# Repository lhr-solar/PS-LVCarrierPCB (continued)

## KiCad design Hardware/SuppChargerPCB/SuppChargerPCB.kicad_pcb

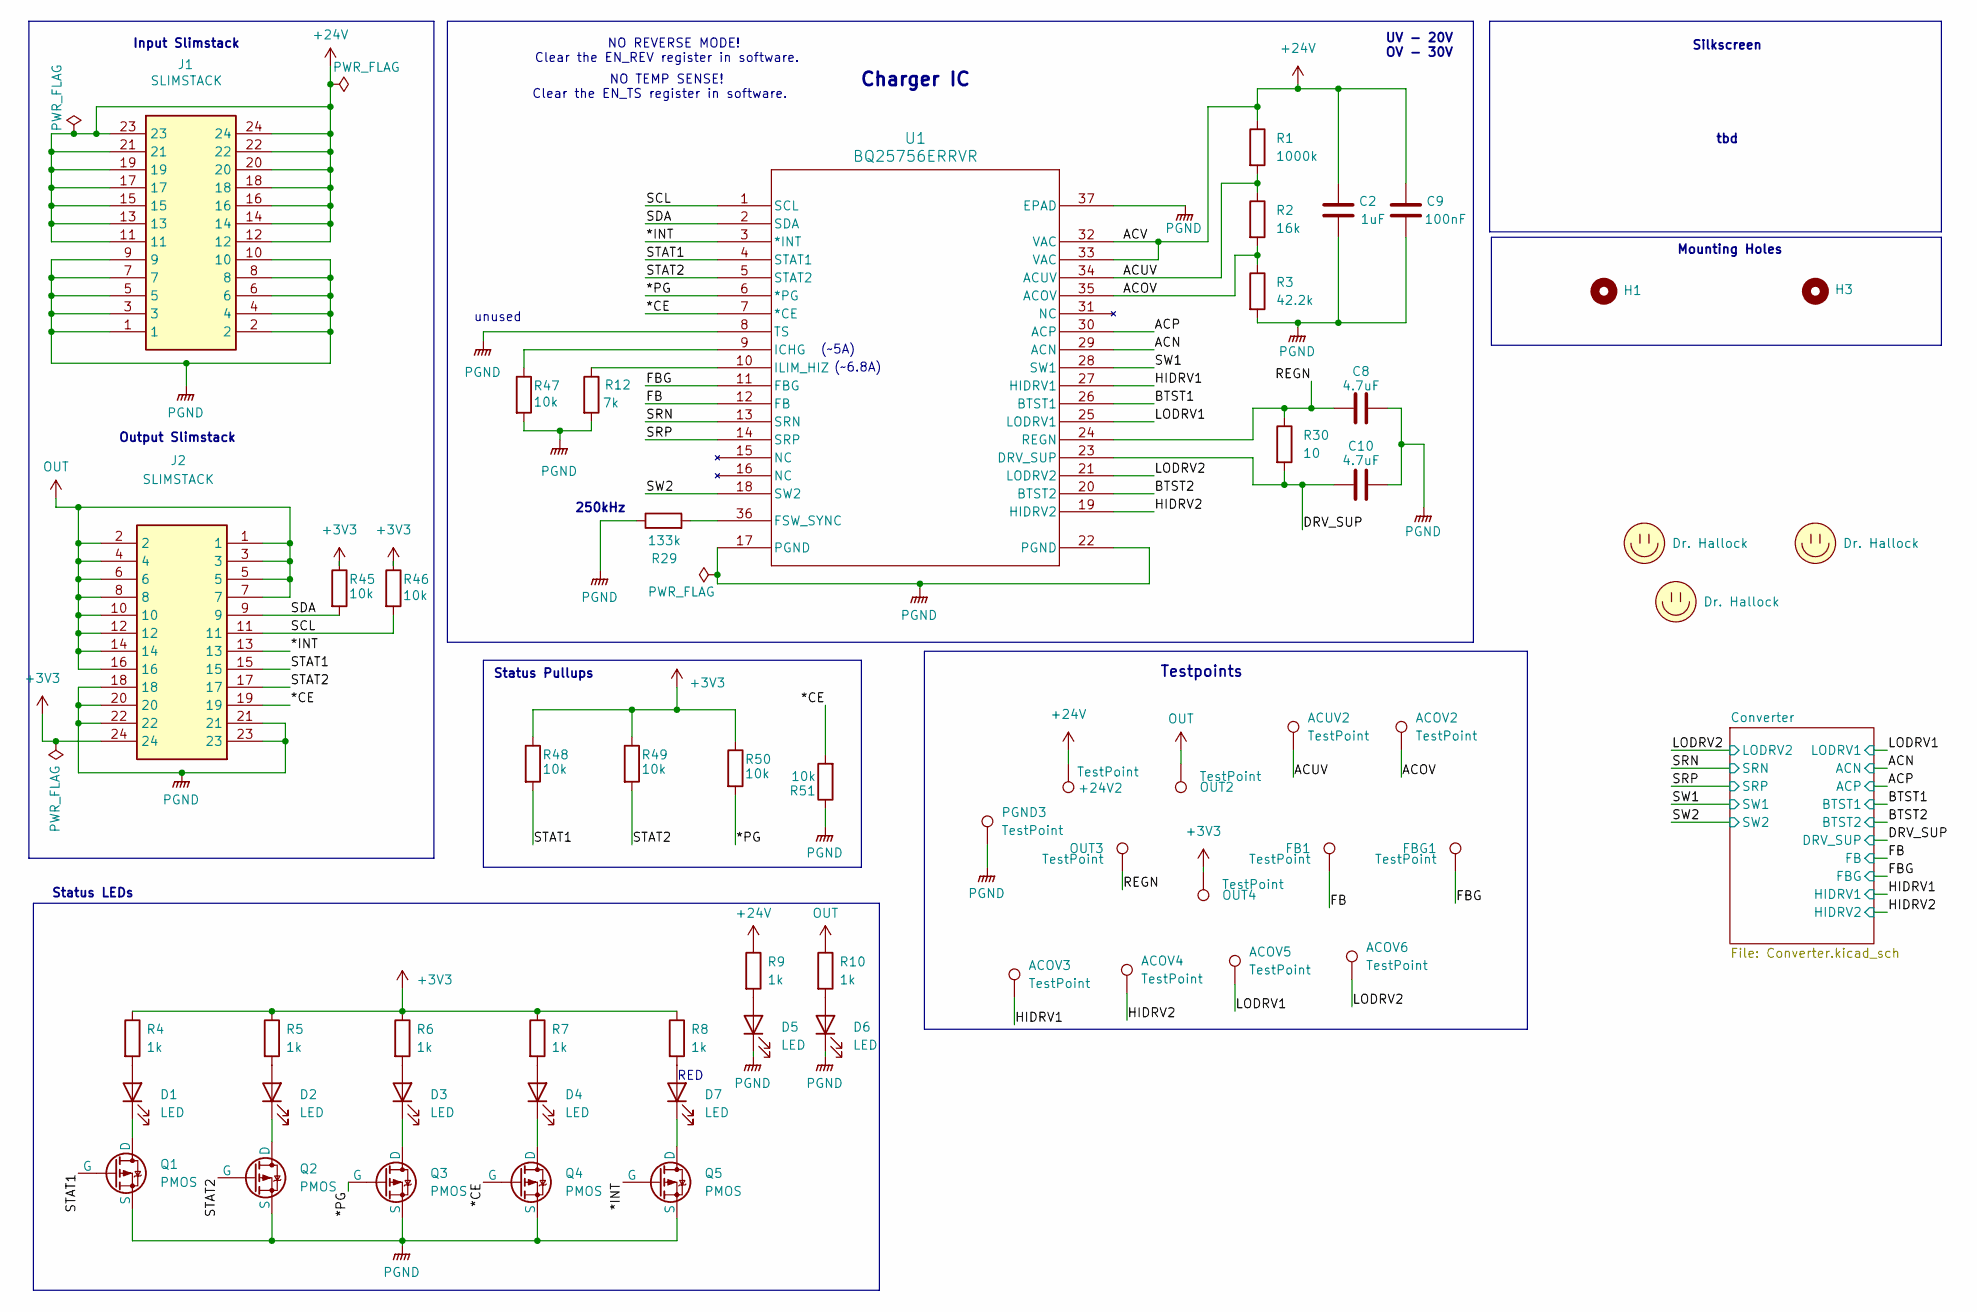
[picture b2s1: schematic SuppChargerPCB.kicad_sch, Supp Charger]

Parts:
+24V2: TestPoint; TestPoint_THTPad_1.0x1.0mm_Drill0.5mm
ACOV2, ACOV3, ACOV4, ACOV5, ACOV6: TestPoint; TestPoint_Pad_1.0x1.0mm
ACUV2: TestPoint; TestPoint_Pad_1.0x1.0mm
C2: 1uF; C_0603_1608Metric_Pad1.08x0.95mm_HandSolder
C8, C10: 4.7uF; C_0805_2012Metric
C9: 100nF; C_0603_1608Metric_Pad1.08x0.95mm_HandSolder
D1, D2, D3, D4, D5, D6, D7: LED; D_0603_1608Metric
FB1: TestPoint; TestPoint_Pad_1.0x1.0mm
FBG1: TestPoint; TestPoint_Pad_1.0x1.0mm
H1, H3: MountingHole; MountingHole_3.2mm_M3_Pad_TopBottom
J1, J2: SLIMSTACK; 524652470; Mouser Part Number 538-52465-2470
LOGO1: Dr. Hallock; UTSVT_Logo_Symbol
LOGO2: Dr. Hallock; LHRs_LOGO
LOGO3: Dr. Hallock; Hallock_Image_Tiny
OUT2, OUT4: TestPoint; TestPoint_THTPad_1.0x1.0mm_Drill0.5mm
OUT3: TestPoint; TestPoint_Pad_1.0x1.0mm
PGND3: TestPoint; TestPoint_THTPad_1.0x1.0mm_Drill0.5mm
Q1, Q2, Q3, Q4, Q5: PMOS; SOT-23
R1: 1000k; R_0603_1608Metric_Pad0.98x0.95mm_HandSolder
R2: 16k; R_0603_1608Metric_Pad0.98x0.95mm_HandSolder
R3: 42.2k; R_0603_1608Metric_Pad0.98x0.95mm_HandSolder
R4, R5, R6, R7, R8, R9, R10: 1k; R_0603_1608Metric_Pad0.98x0.95mm_HandSolder
R12: 7k; R_0603_1608Metric_Pad0.98x0.95mm_HandSolder
R29: 133k; R_0603_1608Metric_Pad0.98x0.95mm_HandSolder
R30: 10; R_0603_1608Metric_Pad0.98x0.95mm_HandSolder
R45, R46, R47, R48, R49, R50, R51: 10k; R_0603_1608Metric_Pad0.98x0.95mm_HandSolder
U1: BQ25756ERRVR; VQFN36_RRV_TEX

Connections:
+3V3: J2.24, OUT4.1, R4.1, R5.1, R6.1, R7.1, R8.1, R45.1, R46.1, R48.1, R49.1, R50.1
+24V: +24V2.1, C2.1, C9.1, J1.11, J1.12, J1.13, J1.14, J1.15, J1.16, J1.17, J1.18, J1.19, J1.20, J1.21, J1.22, J1.23, J1.24, R1.1, R9.1, U1.32 (VAC), U1.33 (VAC); also elsewhere on the board
/*CE: J2.19, Q4.2 (G), R51.2, U1.7 (*CE)
/*INT: J2.13, Q5.2 (G), U1.3 (*INT)
/*PG: Q3.2 (G), R50.2, U1.6 (*PG)
/ACN: U1.29 (ACN); also elsewhere on the board
/ACOV: ACOV2.1, R2.2, R3.1, U1.35 (ACOV)
/ACP: U1.30 (ACP); also elsewhere on the board
/ACUV: ACUV2.1, R1.2, R2.1, U1.34 (ACUV)
/BTST1: U1.26 (BTST1); also elsewhere on the board
/BTST2: U1.20 (BTST2); also elsewhere on the board
/DRV_SUP: C10.1, R30.2, U1.23 (DRV_SUP); also elsewhere on the board
/FB: FB1.1, U1.12 (FB); also elsewhere on the board
/FBG: FBG1.1, U1.11 (FBG); also elsewhere on the board
/HIDRV1: ACOV3.1, U1.27 (HIDRV1); also elsewhere on the board
/HIDRV2: ACOV4.1, U1.19 (HIDRV2); also elsewhere on the board
/LODRV1: ACOV5.1, U1.25 (LODRV1); also elsewhere on the board
/LODRV2: ACOV6.1, U1.21 (LODRV2); also elsewhere on the board
/REGN: C8.1, OUT3.1, R30.1, U1.24 (REGN)
/SCL: J2.11, R46.2, U1.1 (SCL)
/SDA: J2.9, R45.2, U1.2 (SDA)
/SRN: U1.13 (SRN); also elsewhere on the board
/SRP: U1.14 (SRP); also elsewhere on the board
/STAT1: J2.15, Q1.2 (G), R48.2, U1.4 (STAT1)
/STAT2: J2.17, Q2.2 (G), R49.2, U1.5 (STAT2)
/SW1: U1.28 (SW1); also elsewhere on the board
/SW2: U1.18 (SW2); also elsewhere on the board
unnamed: D1.2 (A), R4.2
unnamed: D1.1 (K), Q1.1 (D)
unnamed: D2.2 (A), R5.2
unnamed: D2.1 (K), Q2.1 (D)
unnamed: D3.2 (A), R6.2
unnamed: D3.1 (K), Q3.1 (D)
unnamed: D4.2 (A), R7.2
unnamed: D4.1 (K), Q4.1 (D)
unnamed: D5.2 (A), R9.2
unnamed: D6.2 (A), R10.2
unnamed: D7.2 (A), R8.2
unnamed: D7.1 (K), Q5.1 (D)
unnamed: R29.2, U1.36 (FSW_SYNC)
unnamed: R47.1, U1.9 (ICHG)
unnamed: R12.1, U1.10 (ILIM_HIZ)
OUT: J2.1, J2.2, J2.3, J2.4, J2.5, J2.6, J2.7, J2.8, J2.10, J2.12, J2.14, J2.16, OUT2.1, R10.1; also elsewhere on the board
PGND: C2.2, C8.2, C9.2, C10.2, D5.1 (K), D6.1 (K), J1.1, J1.2, J1.3, J1.4, J1.5, J1.6, J1.7, J1.8, J1.9, J1.10, J2.18, J2.20, J2.21, J2.22, J2.23, PGND3.1, Q1.3 (S), Q2.3 (S), Q3.3 (S), Q4.3 (S), Q5.3 (S), R3.2, R12.2, R29.1, R47.2, R51.1, U1.8 (TS), U1.17 (PGND), U1.22 (PGND), U1.37 (EPAD); also elsewhere on the board

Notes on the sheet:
Testpoints
(~6.8A)
250kHz
Mounting Holes
RED
Status LEDs
Status Pullups
Charger IC
unused
tbd
UV - 20V OV - 30V
Output Slimstack
NO REVERSE MODE! Clear the EN_REV register in software.
Input Slimstack
(~5A)
Silkscreen
NO TEMP SENSE! Clear the EN_TS register in software.

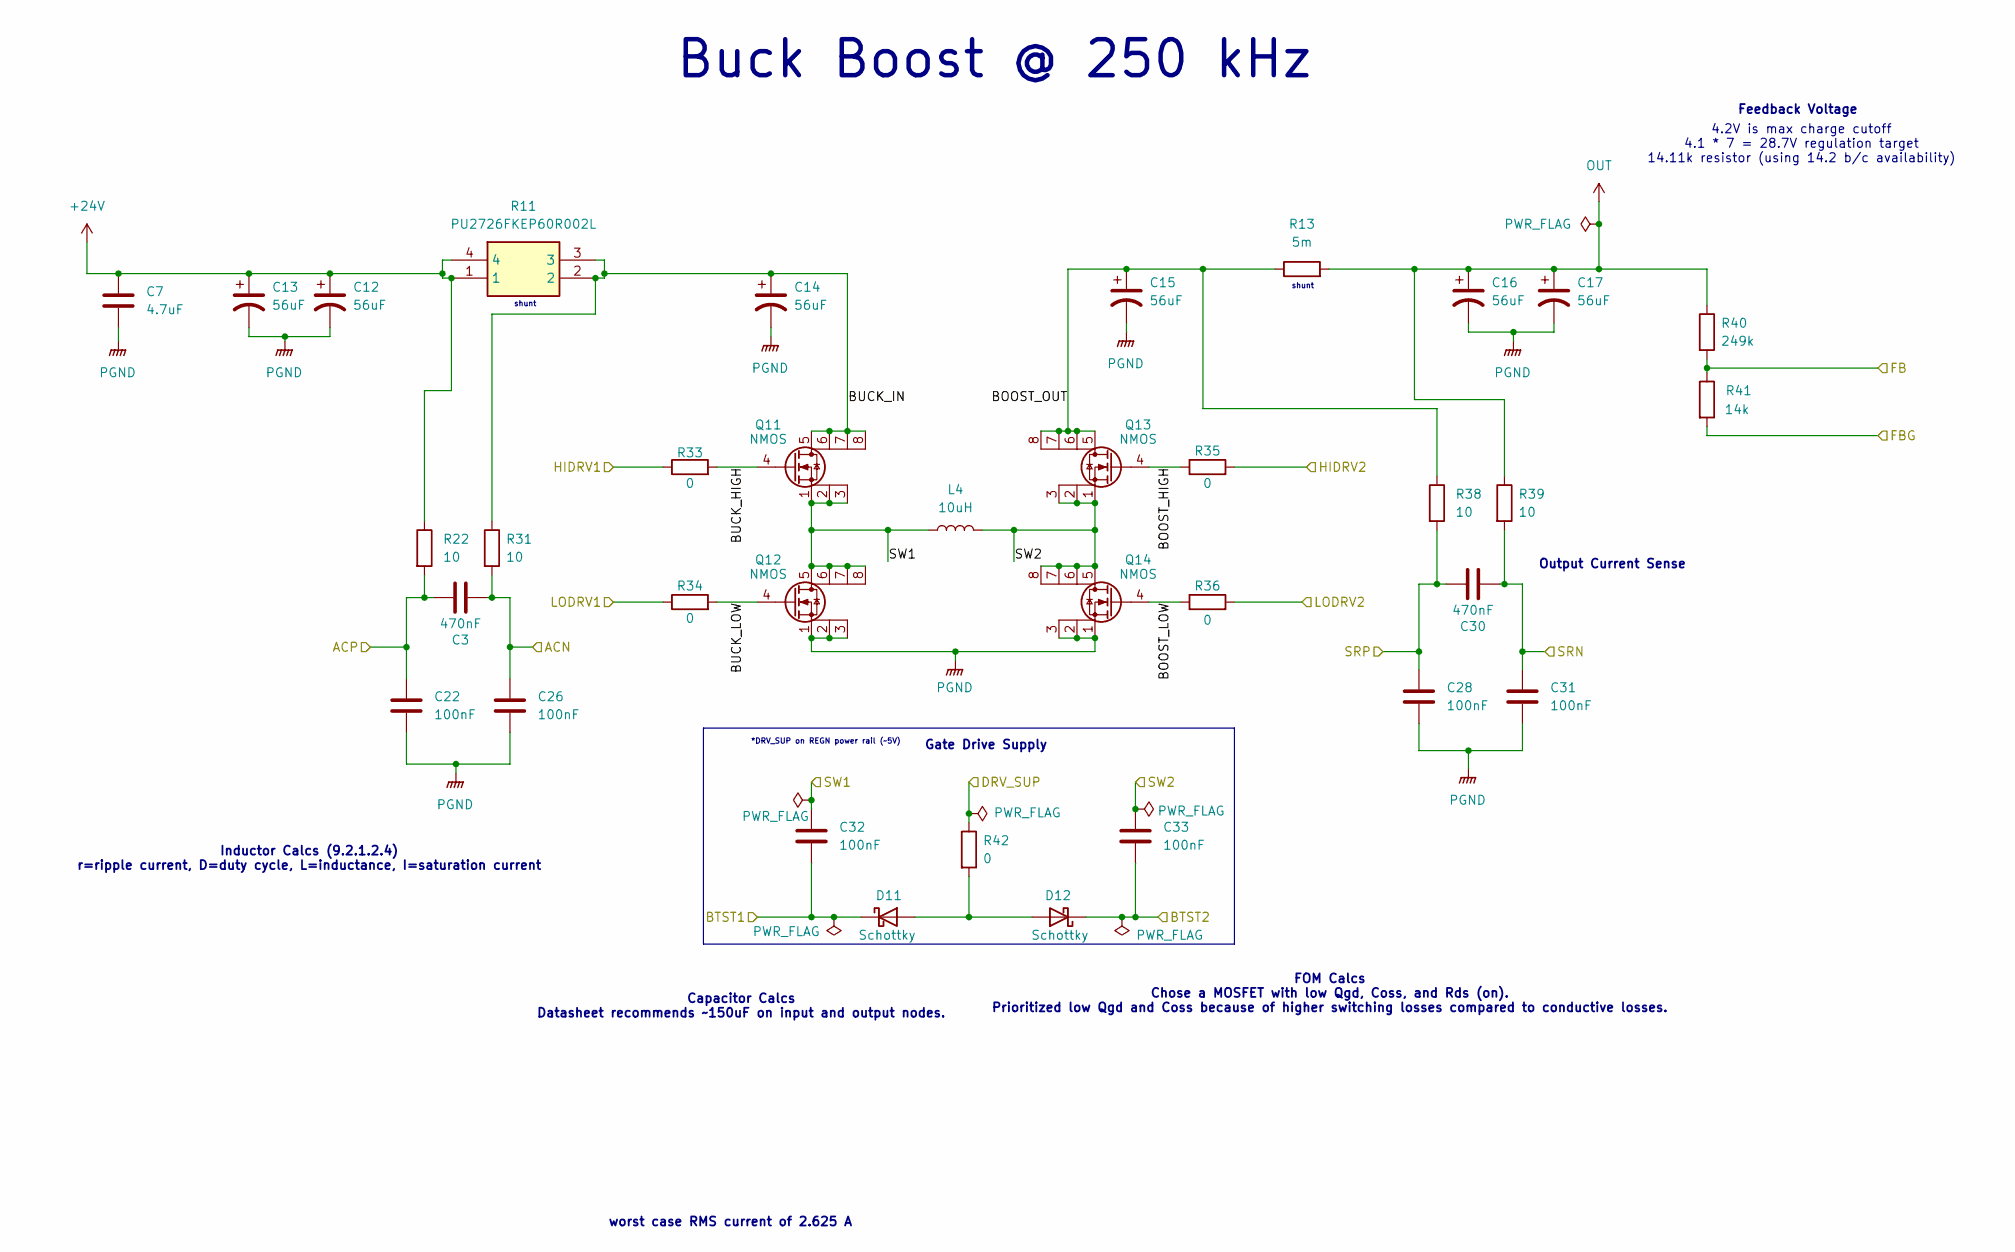
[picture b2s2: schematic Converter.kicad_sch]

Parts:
C3, C30: 470nF; C_0603_1608Metric_Pad1.08x0.95mm_HandSolder
C7: 4.7uF; C_0805_2012Metric
C12, C13, C14, C15, C16, C17: 56uF; CAPAE660X550N
C22, C26, C28, C31, C32, C33: 100nF; C_0603_1608Metric_Pad1.08x0.95mm_HandSolder
D11, D12: Schottky; D_SOD-123F
L4: 10uH; WE-HCC_807021
Q11, Q12, Q13, Q14: NMOS; MOSFET_3DN-T1-GE3_VIS
R11: PU2726FKEP60R002L; Manufacturer_Part_Number PU2726FKEP60R002L
R13: 5m; R_1210_3225Metric_Pad1.30x2.65mm_HandSolder
R22, R31, R38, R39: 10; R_0603_1608Metric_Pad0.98x0.95mm_HandSolder
R33, R34, R35, R36, R42: 0; R_0603_1608Metric_Pad0.98x0.95mm_HandSolder
R40: 249k; R_0603_1608Metric_Pad0.98x0.95mm_HandSolder
R41: 14k; R_0603_1608Metric_Pad0.98x0.95mm_HandSolder

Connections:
+24V: C7.1, C12.1, C13.1, R11.1, R11.4, R22.1; also elsewhere on the board
/ACN: C3.1, C26.1, R31.2; also elsewhere on the board
/ACP: C3.2, C22.1, R22.2; also elsewhere on the board
/BTST1: C32.2, D11.1 (K); also elsewhere on the board
/BTST2: C33.2, D12.1 (K); also elsewhere on the board
/Converter/BOOST_HIGH: Q13.4 (G), R35.1
/Converter/BOOST_LOW: Q14.4 (G), R36.1
/Converter/BOOST_OUT: C15.1, Q13.5 (D), Q13.6 (D), Q13.7 (D), Q13.8 (D), R13.1, R38.1
/Converter/BUCK_HIGH: Q11.4 (G), R33.2
/Converter/BUCK_IN: C14.1, Q11.5 (D), Q11.6 (D), Q11.7 (D), Q11.8 (D), R11.2, R11.3, R31.1
/Converter/BUCK_LOW: Q12.4 (G), R34.2
/DRV_SUP: R42.1; also elsewhere on the board
/FB: R40.2, R41.1; also elsewhere on the board
/FBG: R41.2; also elsewhere on the board
/HIDRV1: R33.1; also elsewhere on the board
/HIDRV2: R35.2; also elsewhere on the board
/LODRV1: R34.1; also elsewhere on the board
/LODRV2: R36.2; also elsewhere on the board
/SRN: C30.1, C31.1, R39.2; also elsewhere on the board
/SRP: C28.1, C30.2, R38.2; also elsewhere on the board
/SW1: C32.1, L4.1, Q11.1 (S), Q11.2 (S), Q11.3 (S), Q12.5 (D), Q12.6 (D), Q12.7 (D), Q12.8 (D); also elsewhere on the board
/SW2: C33.1, L4.2 (1), Q13.1 (S), Q13.2 (S), Q13.3 (S), Q14.5 (D), Q14.6 (D), Q14.7 (D), Q14.8 (D); also elsewhere on the board
unnamed: D11.2 (A), D12.2 (A), R42.2
OUT: C16.1, C17.1, R13.2, R39.1, R40.1; also elsewhere on the board
PGND: C7.2, C12.2, C13.2, C14.2, C15.2, C16.2, C17.2, C22.2, C26.2, C28.2, C31.2, Q12.1 (S), Q12.2 (S), Q12.3 (S), Q14.1 (S), Q14.2 (S), Q14.3 (S); also elsewhere on the board

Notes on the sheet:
Feedback Voltage
4.2V is max charge cutoff 4.1 * 7 = 28.7V regulation target 14.11k resistor (using 14.2 b/c availability)
Inductor Calcs (9.2.1.2.4) r=ripple current, D=duty cycle, L=inductance, I=saturation current
worst case RMS current of 2.625 A
Buck Boost @ 250 kHz
shunt
FOM Calcs Chose a MOSFET with low Qgd, Coss, and Rds (on). Prioritized low Qgd and Coss because of higher switching losses compared to conductive losses.
*DRV_SUP on REGN power rail (~5V)
Output Current Sense
Capacitor Calcs Datasheet recommends ~150uF on input and output nodes.
Gate Drive Supply

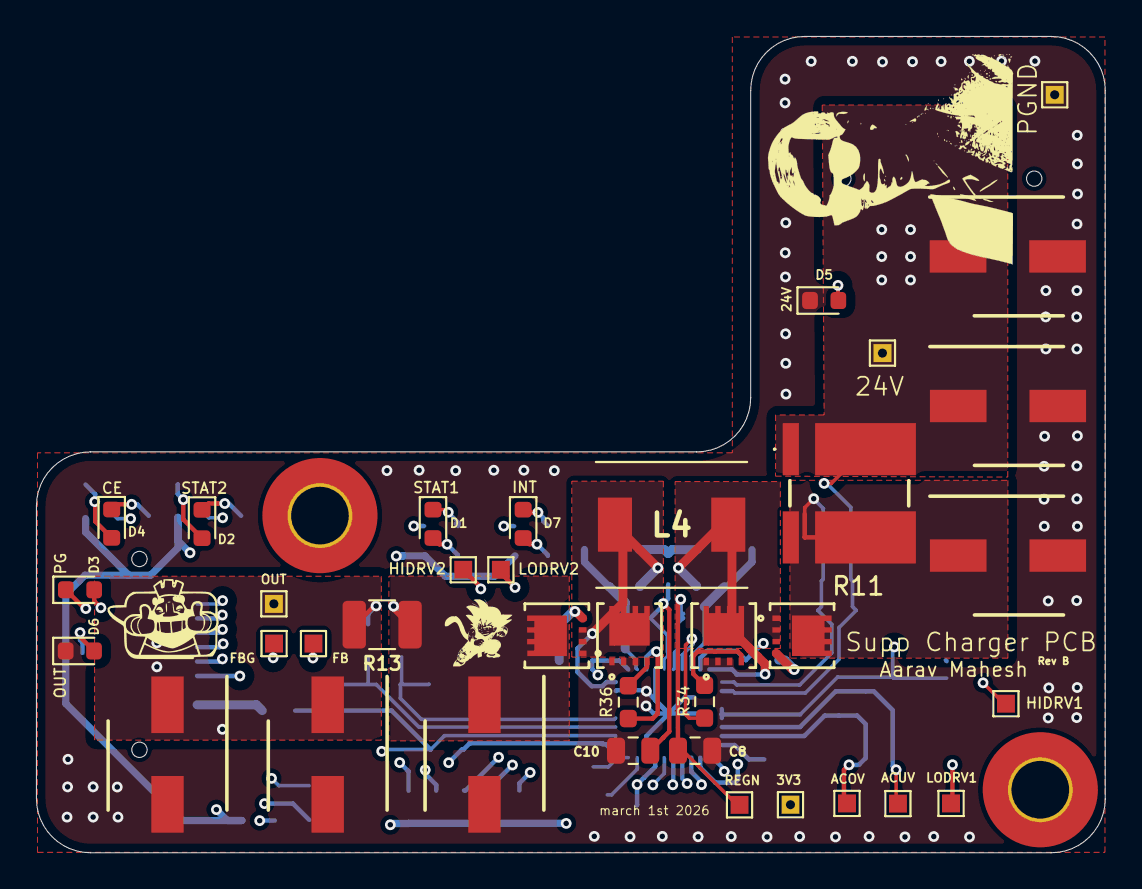
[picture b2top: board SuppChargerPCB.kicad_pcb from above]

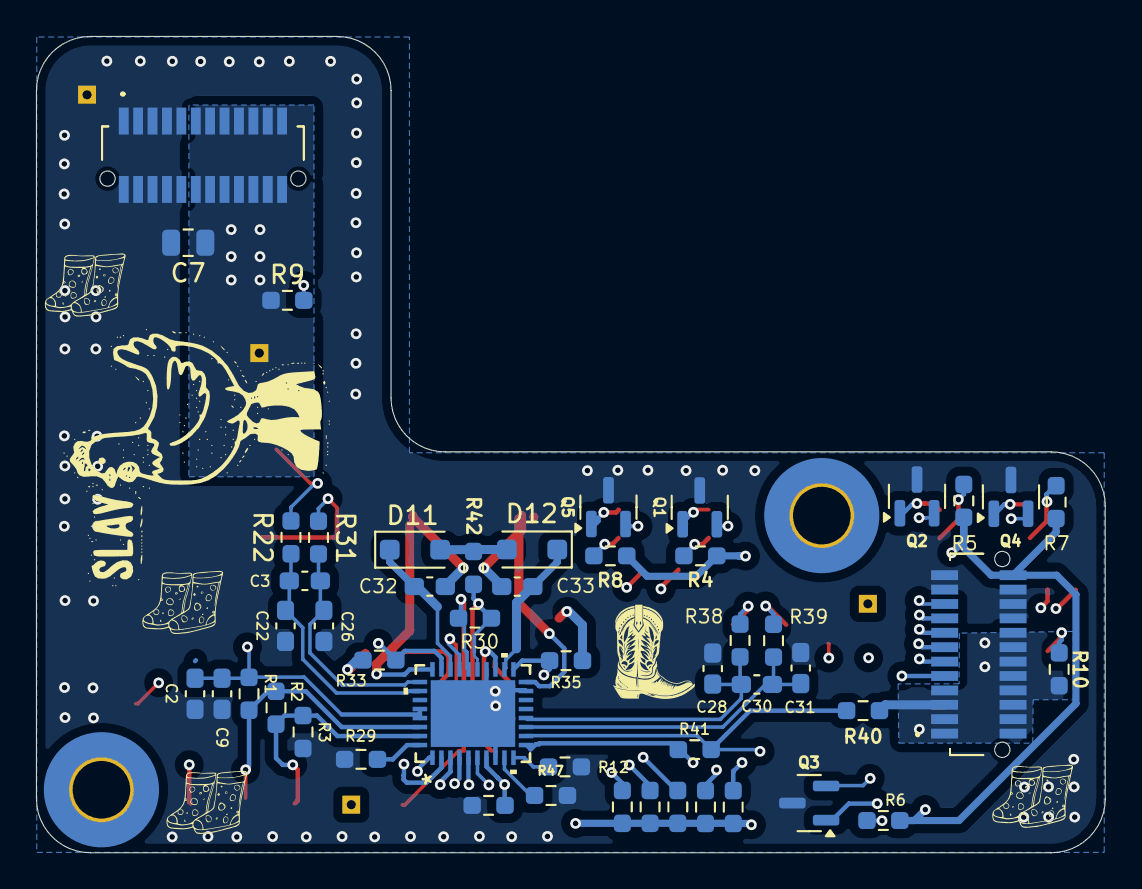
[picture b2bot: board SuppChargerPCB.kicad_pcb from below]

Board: 4 copper layers, 59.4 x 45.4 mm, 92 parts (50 on the bottom side), 51 nets.

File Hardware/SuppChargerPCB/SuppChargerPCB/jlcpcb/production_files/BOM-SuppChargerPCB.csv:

Comment,Designator,Footprint,LCSC,Quantity
0,"R33,R34,R35,R36,R42",R_0603_1608Metric_Pad0.98x0.95mm_HandSolder,C21189,5
10,"R22,R30,R31,R38,R39",R_0603_1608Metric_Pad0.98x0.95mm_HandSolder,C313648,5
1000k,R1,R_0603_1608Metric_Pad0.98x0.95mm_HandSolder,C22935,1
100nF,"C22,C26,C28,C31,C32,C33,C9",C_0603_1608Metric_Pad1.08x0.95mm_HandSolder,C14663,7
10k,"R45,R46,R47,R48,R49,R50,R51",R_0603_1608Metric_Pad0.98x0.95mm_HandSolder,C25804,7
133k,R29,R_0603_1608Metric_Pad0.98x0.95mm_HandSolder,C22870,1
14.2K,R41,R_0603_1608Metric_Pad0.98x0.95mm_HandSolder,C22803,1
16k,R2,R_0603_1608Metric_Pad0.98x0.95mm_HandSolder,C4210,1
1k,"R10,R4,R5,R6,R7,R8,R9",R_0603_1608Metric_Pad0.98x0.95mm_HandSolder,C21190,7
1uF,C2,C_0603_1608Metric_Pad1.08x0.95mm_HandSolder,C15849,1
249k,R40,R_0603_1608Metric_Pad0.98x0.95mm_HandSolder,C22918,1
4.7uF,"C10,C7,C8",C_0805_2012Metric,C98192,3
42.2k,R3,R_0603_1608Metric_Pad0.98x0.95mm_HandSolder,C23167,1
470nF,"C3,C30",C_0603_1608Metric_Pad1.08x0.95mm_HandSolder,C77572,2
7.06k,R12,R_0603_1608Metric_Pad0.98x0.95mm_HandSolder,C861561,1
BQ25756ERRVR,U1,VQFN36_RRV_TEX,C22427194,1
NMOS,"Q1,Q2,Q3,Q4,Q5",SOT95P237X112-3N,C67272,5
Schottky,"D11,D12",D_SOD-123F,C49861250,2
5m,R13,R_1218_3246Metric_Pad1.22x4.75mm_HandSolder,,1
Dr. Hallock,LOGO3,Hallock_Image_Tiny,,1
56uF,C15,CAPAE660X550N,,1
PU2726FKEP60R002L,R11,PU2726FKEP60R002L,,1
NMOS,Q13,MOSFET_3DN-T1-GE3_VIS,,1
TestPoint,OUT3,TestPoint_Pad_1.0x1.0mm,,1
TestPoint,FBG1,TestPoint_Pad_1.0x1.0mm,,1
LED,D4,D_0603_1608Metric,,1
56uF,C12,CAPAE660X550N,,1
TestPoint,OUT4,TestPoint_THTPad_1.0x1.0mm_Drill0.5mm,,1
LED,D1,D_0603_1608Metric,,1
NMOS,Q14,MOSFET_3DN-T1-GE3_VIS,,1
TestPoint,ACOV3,TestPoint_Pad_1.0x1.0mm,,1
TestPoint,OUT2,TestPoint_THTPad_1.0x1.0mm_Drill0.5mm,,1
TestPoint,ACOV2,TestPoint_Pad_1.0x1.0mm,,1
56uF,C16,CAPAE660X550N,,1
TestPoint,PGND3,TestPoint_THTPad_1.0x1.0mm_Drill0.5mm,,1
Dr. Hallock,LOGO2,LHRs_LOGO,,1
LED,D3,D_0603_1608Metric,,1
NMOS,Q11,MOSFET_3DN-T1-GE3_VIS,,1
TestPoint,FB1,TestPoint_Pad_1.0x1.0mm,,1
TestPoint,ACOV5,TestPoint_Pad_1.0x1.0mm,,1
56uF,C17,CAPAE660X550N,,1
56uF,C13,CAPAE660X550N,,1
LED,D7,D_0603_1608Metric,,1
NMOS,Q12,MOSFET_3DN-T1-GE3_VIS,,1
LED,D6,D_0603_1608Metric,,1
TestPoint,ACOV6,TestPoint_Pad_1.0x1.0mm,,1
LED,D2,D_0603_1608Metric,,1
2.2uH,L4,BMRA000606302R2MA1,,1
LED,D5,D_0603_1608Metric,,1
TestPoint,ACOV4,TestPoint_Pad_1.0x1.0mm,,1
TestPoint,ACUV2,TestPoint_Pad_1.0x1.0mm,,1
56uF,C14,CAPAE660X550N,,1
SLIMSTACK,J1,524652470,,1
SLIMSTACK,J2,524652470,,1
Dr. Hallock,LOGO1,UTSVT_Logo_Symbol,,1

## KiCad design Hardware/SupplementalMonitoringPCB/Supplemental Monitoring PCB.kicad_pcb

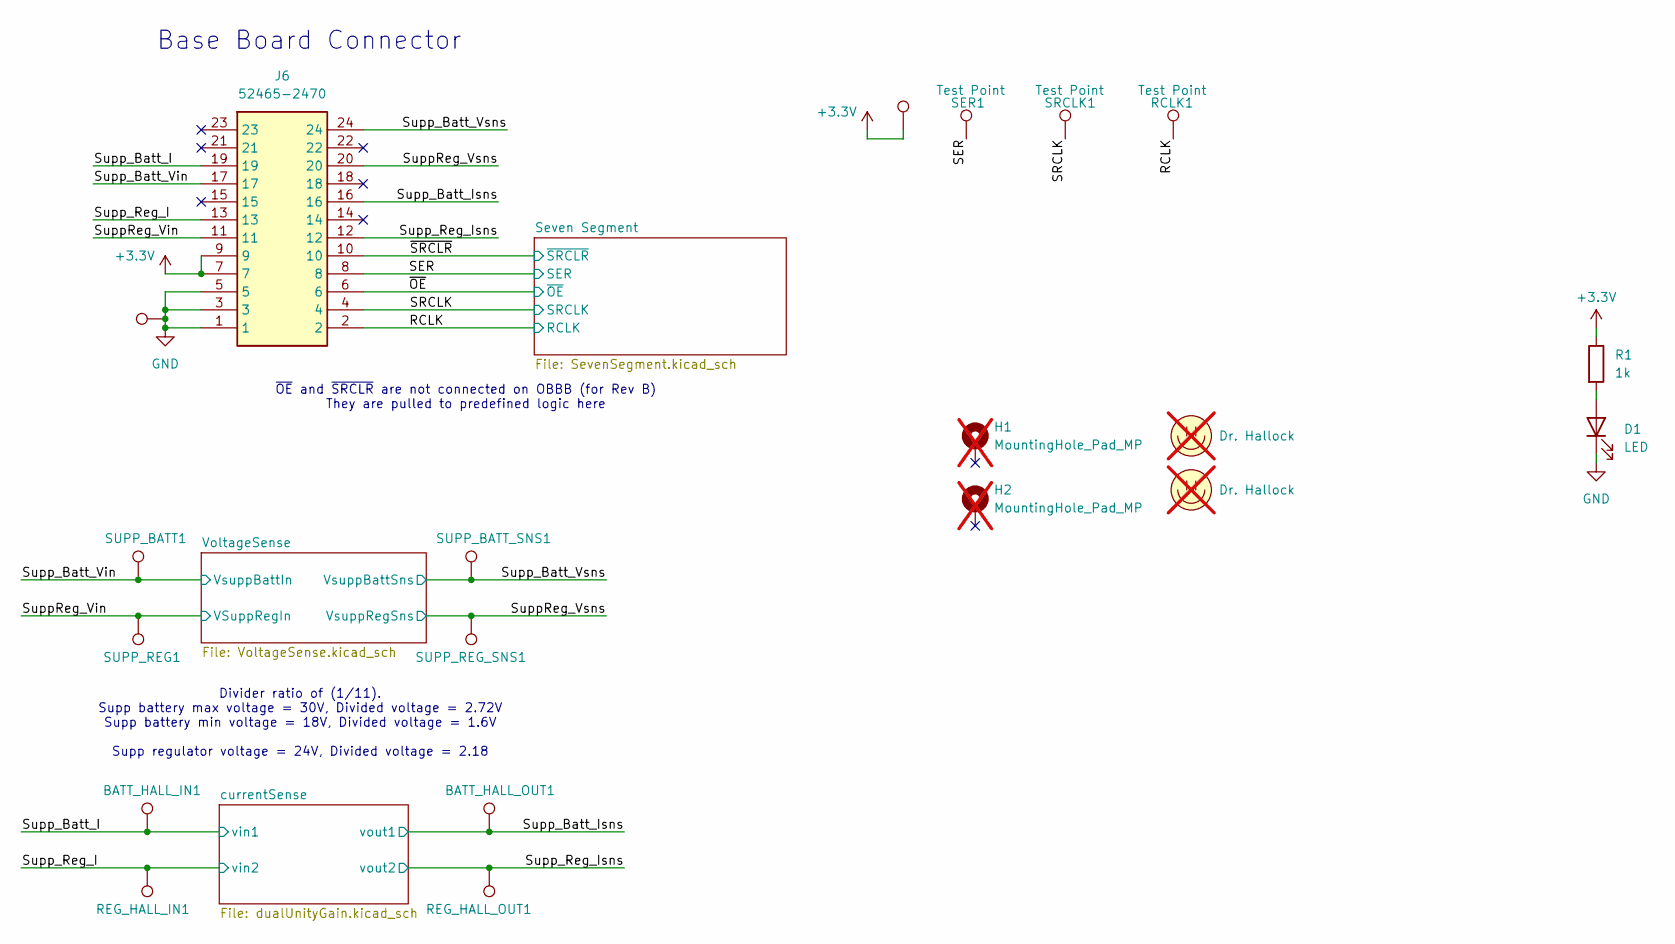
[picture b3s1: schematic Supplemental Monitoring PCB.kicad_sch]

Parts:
BATT_HALL_IN1: TestPoint; TestPoint_THTPad_D2.0mm_Drill1.0mm
BATT_HALL_OUT1: TestPoint; TestPoint_THTPad_D2.0mm_Drill1.0mm
D1: LED; LED_0603_1608Metric; LCSC P/N C7371904
GND1: TestPoint; TestPoint_THTPad_D2.0mm_Drill1.0mm
H1, H2: MountingHole_Pad_MP; MountingHole_3.2mm_M3_Pad_TopBottom; not fitted
J6: 52465-2470; 524652470; Mouser Part Number 538-52465-2470
LOGO1: Dr. Hallock; LHRs_LOGO; not fitted
LOGO2: Dr. Hallock; Hallock_Image_Tiny; not fitted
R1: 1k; R_0603_1608Metric_Pad0.98x0.95mm_HandSolder; LCSC P/N C21190
RCLK1: Test Point; TestPoint_Pad_1.0x1.0mm
REG_HALL_IN1: TestPoint; TestPoint_THTPad_D2.0mm_Drill1.0mm
REG_HALL_OUT1: TestPoint; TestPoint_THTPad_D2.0mm_Drill1.0mm
SER1: Test Point; TestPoint_Pad_1.0x1.0mm
SRCLK1: Test Point; TestPoint_Pad_1.0x1.0mm
SUPP_BATT1: TestPoint; TestPoint_THTPad_D2.0mm_Drill1.0mm
SUPP_BATT_SNS1: TestPoint; TestPoint_THTPad_D2.0mm_Drill1.0mm
SUPP_REG1: TestPoint; TestPoint_THTPad_D2.0mm_Drill1.0mm
SUPP_REG_SNS1: TestPoint; TestPoint_THTPad_D2.0mm_Drill1.0mm
TP_3V3: TestPoint; TestPoint_THTPad_D2.0mm_Drill1.0mm

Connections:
+3.3V: J6.7, J6.9, R1.1, TP_3V3.1; also elsewhere on the board
/RCLK: J6.2, RCLK1.1; also elsewhere on the board
/SER: J6.8, SER1.1; also elsewhere on the board
/SRCLK: J6.4, SRCLK1.1; also elsewhere on the board
/SuppReg_Vin: J6.11, SUPP_REG1.1; also elsewhere on the board
/SuppReg_Vsns: J6.20, SUPP_REG_SNS1.1; also elsewhere on the board
/Supp_Batt_I: BATT_HALL_IN1.1, J6.19; also elsewhere on the board
/Supp_Batt_Isns: BATT_HALL_OUT1.1, J6.16; also elsewhere on the board
/Supp_Batt_Vin: J6.17, SUPP_BATT1.1; also elsewhere on the board
/Supp_Batt_Vsns: J6.24, SUPP_BATT_SNS1.1; also elsewhere on the board
/Supp_Reg_I: J6.13, REG_HALL_IN1.1; also elsewhere on the board
/Supp_Reg_Isns: J6.12, REG_HALL_OUT1.1; also elsewhere on the board
/~OE: J6.6; also elsewhere on the board
/~SRCLR: J6.10; also elsewhere on the board
GND: D1.1 (K), GND1.1, J6.1, J6.3, J6.5; also elsewhere on the board
unnamed: D1.2 (A), R1.2

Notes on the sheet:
Base Board Connector
~{OE} and ~{SRCLR} are not connected on OBBB (for Rev B) They are pulled to predefined logic here
Divider ratio of (1/11). Supp battery max voltage = 30V, Divided voltage = 2.72V Supp battery min voltage = 18V, Divided voltage = 1.6V Supp regulator voltage = 24V, Divided voltage = 2.18

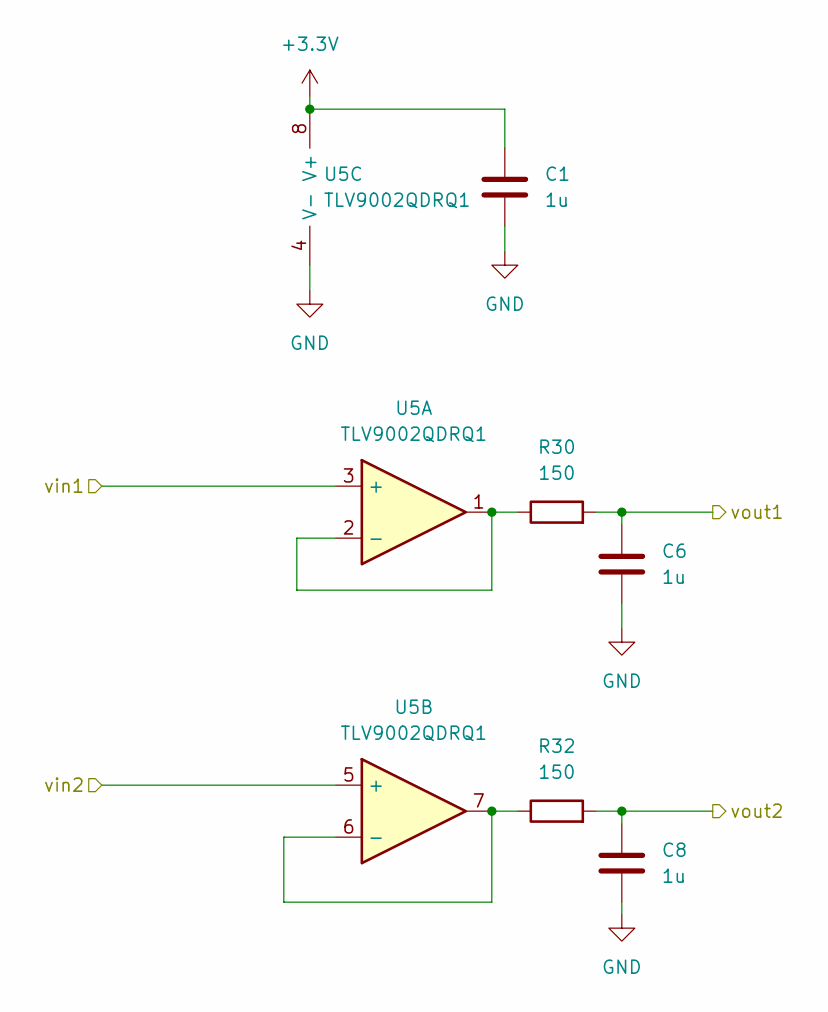
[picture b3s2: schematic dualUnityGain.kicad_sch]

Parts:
C1, C6, C8: 1u; C_0603_1608Metric_Pad1.08x0.95mm_HandSolder; LCSC P/N C15849
R30, R32: 150; R_0603_1608Metric_Pad0.98x0.95mm_HandSolder; LCSC P/N C22808
U5: TLV9002QDRQ1; SOIC-8_3.9x4.9mm_P1.27mm; Mouser P/N 595-TLV9002QDRQ1

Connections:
+3.3V: C1.1, U5.8 (V+); also elsewhere on the board
/Supp_Batt_I: U5.3 (+); also elsewhere on the board
/Supp_Batt_Isns: C6.1, R30.2; also elsewhere on the board
/Supp_Reg_I: U5.5 (+); also elsewhere on the board
/Supp_Reg_Isns: C8.1, R32.2; also elsewhere on the board
GND: C1.2, C6.2, C8.2, U5.4 (V-); also elsewhere on the board
unnamed: R30.1, U5.1, U5.2 (-)
unnamed: R32.1, U5.6 (-), U5.7

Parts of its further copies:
C2, C7, C9: 1u; C_0603_1608Metric_Pad1.08x0.95mm_HandSolder; LCSC P/N C15849
R31, R33: 150; R_0603_1608Metric_Pad0.98x0.95mm_HandSolder; LCSC P/N C22808
U6: TLV9002QDRQ1; SOIC-8_3.9x4.9mm_P1.27mm; Mouser P/N 595-TLV9002QDRQ1

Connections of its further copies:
+3.3V: C2.1, U6.8 (V+); also elsewhere on the board
/SuppReg_Vsns: C9.1, R33.2; also elsewhere on the board
/Supp_Batt_Vsns: C7.1, R31.2; also elsewhere on the board
/VoltageSense/vin1_divided: U6.3 (+); also elsewhere on the board
/VoltageSense/vin2_divided: U6.5 (+); also elsewhere on the board
GND: C2.2, C7.2, C9.2, U6.4 (V-); also elsewhere on the board
unnamed: R31.1, U6.1, U6.2 (-)
unnamed: R33.1, U6.6 (-), U6.7

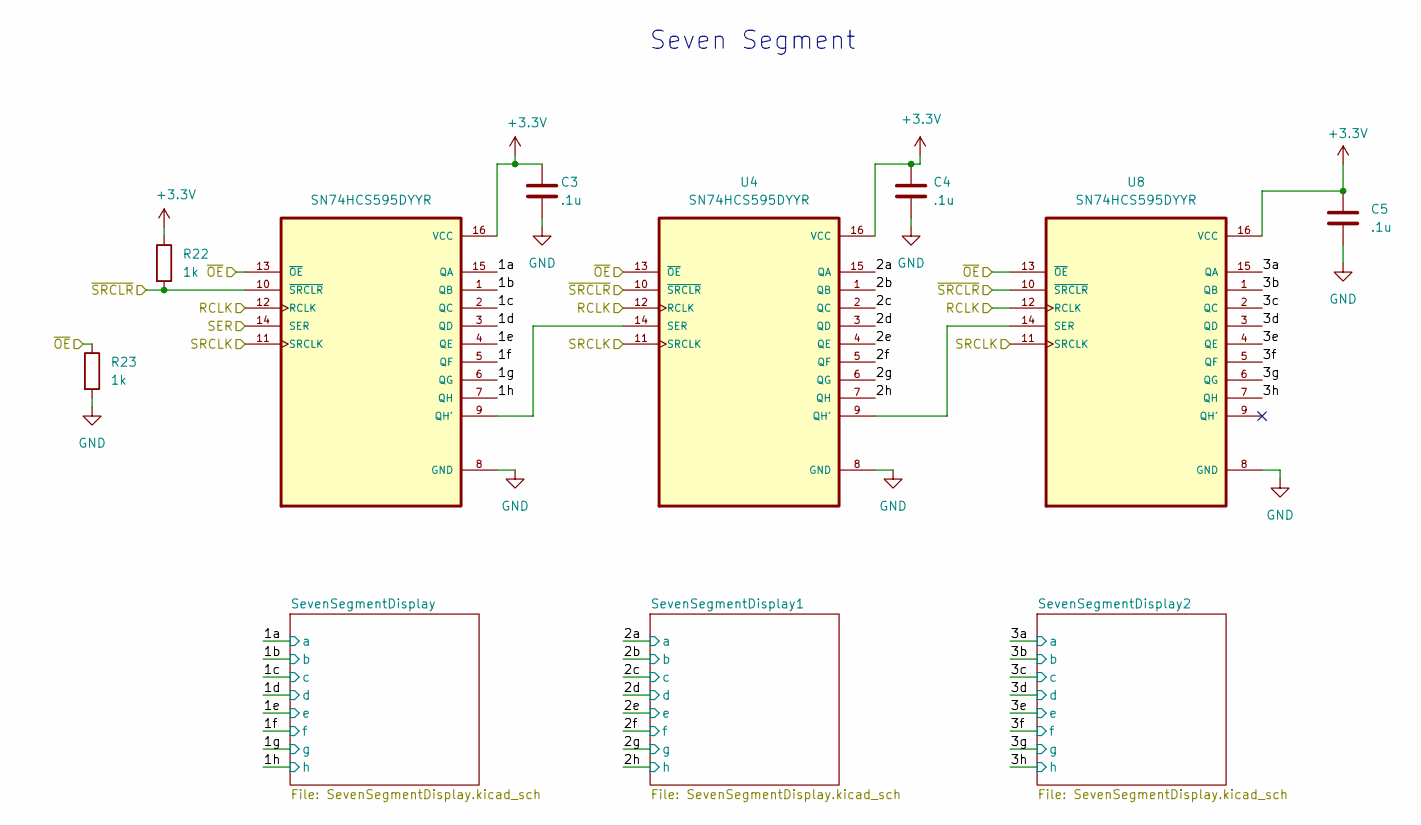
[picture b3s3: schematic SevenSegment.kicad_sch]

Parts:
C3, C4, C5: .1u; C_0603_1608Metric_Pad1.08x0.95mm_HandSolder; LCSC P/N C14663
R22, R23: 1k; R_0603_1608Metric_Pad0.98x0.95mm_HandSolder; LCSC P/N C21190
U2, U4, U8: SN74HCS595DYYR; SNx4HC595

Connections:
+3.3V: C3.1, C4.1, C5.1, R22.1, U2.16 (VCC), U4.16 (VCC), U8.16 (VCC); also elsewhere on the board
/RCLK: U2.12 (RCLK), U4.12 (RCLK), U8.12 (RCLK); also elsewhere on the board
/SER: U2.14 (SER); also elsewhere on the board
/SRCLK: U2.11 (SRCLK), U4.11 (SRCLK), U8.11 (SRCLK); also elsewhere on the board
/Seven Segment/1a: U2.15 (QA); also elsewhere on the board
/Seven Segment/1b: U2.1 (QB); also elsewhere on the board
/Seven Segment/1c: U2.2 (QC); also elsewhere on the board
/Seven Segment/1d: U2.3 (QD); also elsewhere on the board
/Seven Segment/1e: U2.4 (QE); also elsewhere on the board
/Seven Segment/1f: U2.5 (QF); also elsewhere on the board
/Seven Segment/1g: U2.6 (QG); also elsewhere on the board
/Seven Segment/1h: U2.7 (QH); also elsewhere on the board
/Seven Segment/2a: U4.15 (QA); also elsewhere on the board
/Seven Segment/2b: U4.1 (QB); also elsewhere on the board
/Seven Segment/2c: U4.2 (QC); also elsewhere on the board
/Seven Segment/2d: U4.3 (QD); also elsewhere on the board
/Seven Segment/2e: U4.4 (QE); also elsewhere on the board
/Seven Segment/2f: U4.5 (QF); also elsewhere on the board
/Seven Segment/2g: U4.6 (QG); also elsewhere on the board
/Seven Segment/2h: U4.7 (QH); also elsewhere on the board
/Seven Segment/3a: U8.15 (QA); also elsewhere on the board
/Seven Segment/3b: U8.1 (QB); also elsewhere on the board
/Seven Segment/3c: U8.2 (QC); also elsewhere on the board
/Seven Segment/3d: U8.3 (QD); also elsewhere on the board
/Seven Segment/3e: U8.4 (QE); also elsewhere on the board
/Seven Segment/3f: U8.5 (QF); also elsewhere on the board
/Seven Segment/3g: U8.6 (QG); also elsewhere on the board
/Seven Segment/3h: U8.7 (QH); also elsewhere on the board
/~OE: R23.1, U2.13 (~OE), U4.13 (~OE), U8.13 (~OE); also elsewhere on the board
/~SRCLR: R22.2, U2.10 (~SRCLR), U4.10 (~SRCLR), U8.10 (~SRCLR); also elsewhere on the board
GND: C3.2, C4.2, C5.2, R23.2, U2.8 (GND), U4.8 (GND), U8.8 (GND); also elsewhere on the board
unnamed: U2.9 (QH'), U4.14 (SER)
unnamed: U4.9 (QH'), U8.14 (SER)

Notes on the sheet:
Seven Segment

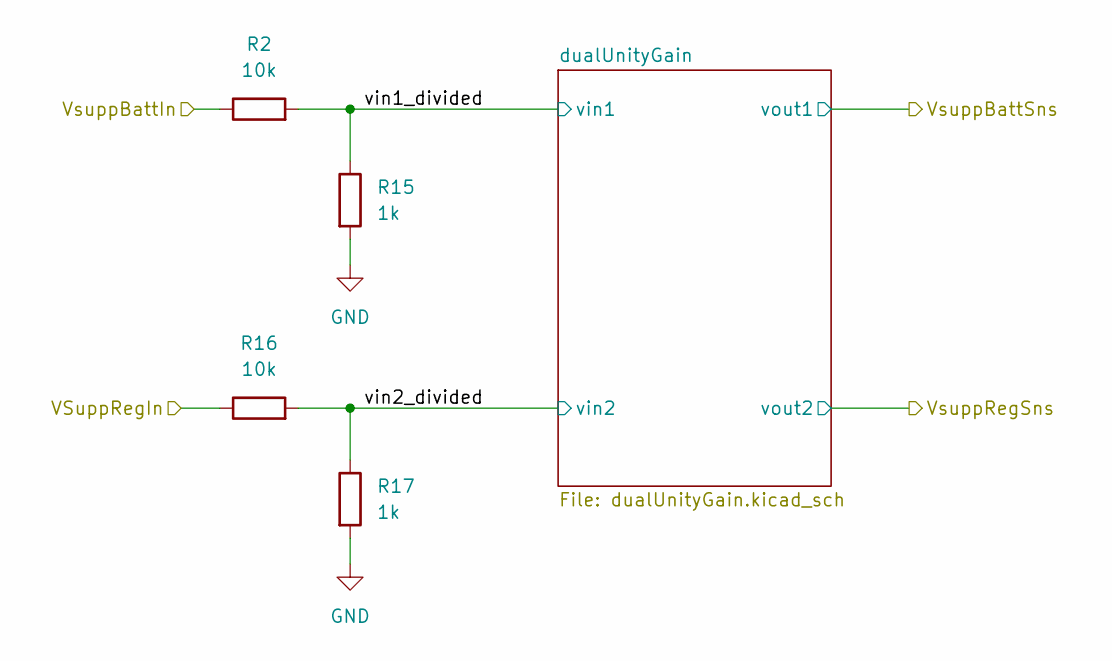
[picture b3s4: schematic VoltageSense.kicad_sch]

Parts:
R2, R16: 10k; R_0603_1608Metric_Pad0.98x0.95mm_HandSolder; LCSC P/N C25804
R15, R17: 1k; R_0603_1608Metric_Pad0.98x0.95mm_HandSolder; LCSC P/N C21190

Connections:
/SuppReg_Vin: R16.1; also elsewhere on the board
/Supp_Batt_Vin: R2.1; also elsewhere on the board
/VoltageSense/vin1_divided: R2.2, R15.1; also elsewhere on the board
/VoltageSense/vin2_divided: R16.2, R17.1; also elsewhere on the board
GND: R15.2, R17.2; also elsewhere on the board

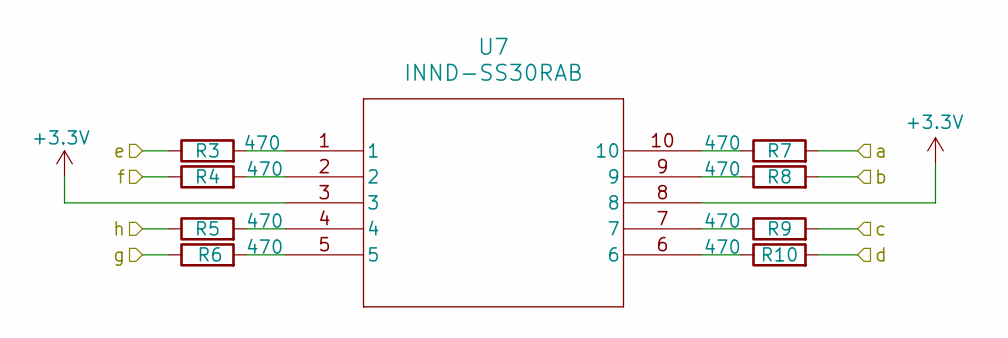
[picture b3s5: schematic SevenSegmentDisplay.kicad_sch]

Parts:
R3, R4, R5, R6, R7, R8, R9, R10: 470; R_0603_1608Metric_Pad0.98x0.95mm_HandSolder; LCSC P/N C23179
U7: INND-SS30RAB; INND-TS30RAB_INL

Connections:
+3.3V: U7.3, U7.8; also elsewhere on the board
/Seven Segment/2a: R7.2; also elsewhere on the board
/Seven Segment/2b: R8.2; also elsewhere on the board
/Seven Segment/2c: R9.2; also elsewhere on the board
/Seven Segment/2d: R10.2; also elsewhere on the board
/Seven Segment/2e: R3.1; also elsewhere on the board
/Seven Segment/2f: R4.1; also elsewhere on the board
/Seven Segment/2g: R6.1; also elsewhere on the board
/Seven Segment/2h: R5.1; also elsewhere on the board
unnamed: R3.2, U7.1
unnamed: R4.2, U7.2
unnamed: R5.2, U7.4
unnamed: R6.2, U7.5
unnamed: R7.1, U7.10
unnamed: R8.1, U7.9
unnamed: R9.1, U7.7
unnamed: R10.1, U7.6

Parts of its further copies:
R11, R12, R13, R14, R18, R19, R20, R21, R34, R35, R36, R37, R38, R39, R40, R41: 470; R_0603_1608Metric_Pad0.98x0.95mm_HandSolder; LCSC P/N C23179
U10, U11: INND-SS30RAB; INND-TS30RAB_INL

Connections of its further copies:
+3.3V: U10.3, U10.8, U11.3, U11.8; also elsewhere on the board
/Seven Segment/1a: R34.2; also elsewhere on the board
/Seven Segment/1b: R36.2; also elsewhere on the board
/Seven Segment/1c: R38.2; also elsewhere on the board
/Seven Segment/1d: R40.2; also elsewhere on the board
/Seven Segment/1e: R35.1; also elsewhere on the board
/Seven Segment/1f: R37.1; also elsewhere on the board
/Seven Segment/1g: R41.1; also elsewhere on the board
/Seven Segment/1h: R39.1; also elsewhere on the board
/Seven Segment/3a: R18.2; also elsewhere on the board
/Seven Segment/3b: R19.2; also elsewhere on the board
/Seven Segment/3c: R20.2; also elsewhere on the board
/Seven Segment/3d: R21.2; also elsewhere on the board
/Seven Segment/3e: R11.1; also elsewhere on the board
/Seven Segment/3f: R12.1; also elsewhere on the board
/Seven Segment/3g: R14.1; also elsewhere on the board
/Seven Segment/3h: R13.1; also elsewhere on the board
unnamed: R11.2, U10.1
unnamed: R12.2, U10.2
unnamed: R13.2, U10.4
unnamed: R14.2, U10.5
unnamed: R18.1, U10.10
unnamed: R19.1, U10.9
unnamed: R20.1, U10.7
unnamed: R21.1, U10.6
unnamed: R34.1, U11.10
unnamed: R35.2, U11.1
unnamed: R36.1, U11.9
unnamed: R37.2, U11.2
unnamed: R38.1, U11.7
unnamed: R39.2, U11.4
unnamed: R40.1, U11.6
unnamed: R41.2, U11.5
